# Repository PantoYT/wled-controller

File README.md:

# wled-controller

Carrier boards for an ESP32 DevKit (30-pin) running WLED with 5 V addressable strips
(WS2812B), plus printed mounts for them. The boards are generated by Python scripts against
KiCad's API, routed by a small A* router written for them, and the printed mounts are
checked for collisions against the boards' STEP models, including while the board slides in.

| | State | Where |
|---|---|---|
| rev 1.0, 1 channel | built, on the desk | [rev1/](rev1/README.md) |
| rev 2.0 `wall`, 6 channels | **current design, ready to order** | [rev2/](rev2/README.md) |
| wall mount for `wall` | designed, not printed | [enclosure/wall/](enclosure/wall/README.md) |
| base and slide-in case for rev 1.0 | printed | [enclosure/rev1/](enclosure/rev1/README.md) |

## Schematic (rev 2.0 `wall`)

[SVG](docs/schematic-wall.svg). The board is generated from code without a KiCad schematic, so
`rev2/schematic.py` draws this from a net list and `schematic.py --check` compares that list
with the routed board pad by pad (28 nets, 0 differences on 2026-10-20).

## Folders

| Folder | What is in it |
|---|---|
| `jlc/` | the one file to upload to JLCPCB |
| `rev1/` | rev 1.0: generator, router, KiCad board, STEP, Gerbers, renders, BOM |
| `rev2/` | rev 2.0: generator (`--size wall`, the old layouts still build), router, the `wall` board, its STEP, renders, back-side art in `art/` |
| `rev2/old-variants/` | layouts that were drawn and dropped: `phi` (6 ch with JST-XH), `phi4` (4 ch, status LEDs), `120`, `100` |
| `enclosure/` | printed parts, one folder per board |
| `purchases/` | costs, TME quick-buy lists (`quickbuy-v2-wall.txt` is the current one), the cost sheet |
| `footprints/`, `3d/` | footprints and stand-in 3D models shared by both revisions |
| `backups/` | WLED config and presets from the desk controller (local only, not in the repository) |

## Ordering the `wall` board at JLCPCB

Upload `jlc/wled-controller-v2-wall-gerbers.zip`: both copper, mask and silkscreen layers, the
outline and one Excellon drill file. (Locally there is also an `-art` zip with back-side art,
see [rev2/](rev2/README.md); that one is not in the repository.) JLC reads the size from the outline:
100 × 61.8 mm, inside their cheapest 100 × 100 mm bracket.

| Option | Choice |
|---|---|
| Layers | 2 |
| Thickness | 1.6 mm |
| Solder mask | black |
| Silkscreen | white |
| Surface finish | HASL lead-free is enough (no bare-copper art on this version) |
| Copper | 1 oz |
| Mark on the board | JLC prints an order number somewhere unless told otherwise; choose the option that removes it or fixes its place (check the form for its price) |

The board passed KiCad's DRC with 0 violations and 0 unconnected items (2026-10-20), with
0.2 mm clearance and 0.4 mm tracks, both inside JLC's standard limits. Optional back
art is made of 0.25 mm dots; JLC's minimum silkscreen line is 0.15 mm.

TME parts: `purchases/quickbuy-v2-wall.txt`. The rest was already on hand: 100 Ω resistors,
100 nF, two 1000 µF capacitors, the DC jack, a 2-pole 5.08 mm terminal, a 3 A blade fuse.

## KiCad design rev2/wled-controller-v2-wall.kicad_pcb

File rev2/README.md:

# wled-controller rev 2.0

Rev 2.0 drives several strips from one ESP32 DevKit (30-pin) through a 74(A)HCT245. Every
output has its own screw terminal, polyfuse and series resistor; one channel shorting trips
its polyfuse and the others keep running.

**The board to order is `wall`** (`--size wall`, files `wled-controller-v2-wall.*`, Gerbers in
`../jlc/`). The other layouts were drawn first and dropped; their boards, renders and Gerbers
are in `old-variants/`. `gen_board.py --size <x>` still builds any of them, into this folder.

## `wall` (2026-10-20, the one to order)

100 × 61.8 mm, six channels along the bottom edge, numbered right to left.

| CH | 1 | 2 | 3 | 4 | 5 | 6 |
|---|---|---|---|---|---|---|
| GPIO | 4 | 18 | 19 | 21 | 22 | 23 |

- **Per channel:** XY302R 3-pole screw terminal at the bottom edge (pins `+ D -`), RG300-16
  polyfuse (3 A hold, 5.1 A trip), 100 Ω standing resistor, the channel number, its GPIO, and
  an empty box to write the strip's name in. No JST sockets: the strips' JST SM pairs come
  with leads, and the lead goes straight into the terminal, so no cable is soldered or
  crimped; the strip unplugs at its SM connector.
- **Parts from TME or LCSC.** The footprints take either source, so the parts can come with
  the PCBs from JLC/LCSC in one parcel:

  | Part | TME | LCSC | What the footprint does |
  |---|---|---|---|
  | screw terminal 3P 3.5 mm | XY302R-3P-3.5-GN | KF350-3.5-3P (C474893) | same pads; courtyard covers both bodies (XY302R 0.7 mm behind its pins and 8.5 mm in front, KF350 3.4 / 3.5 mm); XY302R ends flush with the edge, KF350 about 6 mm inside it |
  | polyfuse 3 A | RG300-16 | FRG300-16F (C2687068) | identical size, 5.1 mm pitch |
  | mini blade fuse holder | Keystone 3568 | XF-508P-B-B (C19727305) | Keystone's footprint with the drills opened to 1.9 mm: XFCN's 1.6 x 0.4 mm tabs sit on a 9.80 mm pitch instead of 9.92 |
  | DevKit sockets 1x15, 8.5 mm | SSW-115-01-T-S | KH-2.54FH-1X15P-H8.5 (C2932676) | standard 2.54 mm |
  | shifter, DIP-20 socket | SN74AHCT245N, 1-2199298-6 | C1548096, C72127 | standard DIP-20 |

  Lists: `../purchases/quickbuy-v2-wall.txt` (TME) and `../purchases/lcsc-bom-wall.csv` (LCSC).
- **Inputs:** the DC jack (5.5/2.1, turned so the plug goes in from the top edge, the open
  end of the wall mount) and the 2-pole screw terminal J2 next to it, in parallel before the
  main blade fuse F1. One source at a time. J2 is for a bigger supply later; the jack has no
  current rating at TME.
- **Main fuse:** 7.5 A at most (track rating, see Power); with the current 3 A supply use the
  spare 3 A fuse.
- **Shifter:** SN74HCT245N or SN74AHCT245N in a socket (HC does not work: it does not see
  3.3 V as high at 5 V). The two unused buffers have their inputs on GND.
- **Nothing tall under the DevKit.** The DevKit sits on one 8.5 mm female header plus its own
  2.5 mm pin plastic, so its underside is 11 mm above the board. C1 (EEUFR1C102L, 11.5 mm
  tall) sits left of the shifter; only the DevKit's own sockets are inside its outline.
- **Mounting holes** H1-H4 at (3.5, 21.0), (3.5, 33.0), (96.52, 39.37), (96.52, 57.15): the
  wall mount's posts, placed where nothing below them passes over a post while the board
  slides in.
- **Back:** "panto", panto-dev.com and the channel to GPIO table. Optional back art:
  `python art/make_art.py picture.png` dithers any picture onto a 0.25 mm grid
  (`art/silk-runs.json`); `gen_board.py --size wall --art art/silk-runs.json` then builds
  `wled-controller-v2-wall-art`, with the art mirrored onto the back silkscreen and cut away
  round every pad and hole pixel by pixel, and `route.py --size wall --art` routes it. The
  board Panto orders carries a wallpaper that is not his to publish, so the picture, the
  `-art` board and its Gerbers stay out of this repository. Silkscreen art costs nothing extra
  at JLC: it is the same white layer.
- **Schematic:** `python schematic.py` draws `../docs/schematic-wall.svg/.png` from the net list
  in the script (schemdraw); `schematic.py --check`, run with KiCad's Python, compares that
  list with the routed board and exits 1 on any difference.
- **Outputs:** `python fab.py wled-controller-v2-wall` writes `../jlc/<name>-gerbers.zip`
  (fails if no drill file came out), the STEP and the renders.
- Routed by `route.py --size wall`: DRC 0 violations, 0 unconnected (2026-10-20). The strip
  terminals' GND pins join the pours solid (they carry the strip current, and the tracks
  starved their thermal spokes).

## `phi4` (dropped 2026-10-20, in `old-variants/`)

Kept for the record; Panto rejected the status LEDs, the gold logo and pixel row, the
hard-coded channel names and the four channels. Its XY302R footprint, wall-mount edge margins
and solid terminal GND carried over to `wall`.

Same 100 × 61.8 mm outline as `phi` (JLC's cheapest bracket), cut down to what the desk and
the TV need, with room for status LEDs and a wall mount (`../enclosure/wall/`):

| CH | GPIO | Strip | LEDs |
|---|---|---|---|
| 1 DESK | 4 | desk, segments as on rev 1.0 | 72 |
| 2 ASUS | 18 | monitor top and sides, from the 1.6 m left over | ~40 |
| 3 TV | 19 | TV perimeter 2 × 91 + 2 × 53 cm, new strip | ~86 |
| 4 AUX | 21 | spare | |

What changed against `phi`:

- **4 channels, not 6.** Three are used; the fourth is a spare. Each cell is 16.5 mm wide
  instead of 12.
- **No JST-XH sockets.** The strips plug in through JST SM pairs, and the pair's pigtail goes
  into the screw terminal, so a strip still unplugs at its SM connector with no hand-made
  leads. JST SM has no PCB socket (wire-to-wire series).
- **No DC jack.** Power comes in through J2 only (Mean Well GST60A05-P1J, 5 V 6 A, through a
  DC-plug-to-screw-terminal adapter). The PC-GK2.1 jack has no current rating at TME, and the
  left edge has to be free for the mount's rail.
- **XY302R terminals with their own footprint**
  (`../footprints/wled.pretty/TerminalBlock_Xinya_XY302R-3_P3.50mm_Horizontal`). From the
  Xinlaiya drawing: pins 0.9 × 0.5 mm (1.03 mm diagonal, fits the 1.2 mm drill), 0.7 mm from
  the back face, body 9.2 mm deep. The pads match KiCad's Phoenix PT footprint, but the body
  does not: on the Phoenix footprint an XY302R would overhang the board edge by about 3 mm.
  The wire entries now end 1.2 mm inside the bottom edge.
- **4 A polyfuses** (`RG400-16`: 4 A hold, 6.8 A trip, same 5.1 mm pitch) and 2.0 mm V_CHn
  tracks, so the TV strip is not capped at 3 A.
- **Two status LEDs per channel**, 3 mm through-hole: yellow DATA on the left, green PWR on
  the right. PWR (10 kΩ from V_CHn) shows that the channel's polyfuse passes current: dark
  means tripped or no input. DATA (470 Ω) hangs on one of the 74HCT245's four spare buffers,
  whose inputs copy that channel's GPIO, so the LED never loads the strip's data line. It
  glows while WLED sends frames (dimly: a frame is a few ms) and stays dark when nothing is
  sent. Values chosen from what is on hand (parts-inventory: 470 Ω × 10, 10 kΩ × 20,
  5 green, 5 yellow); a brighter PWR LED is 1 kΩ.
- **Look:** black mask, ENIG, the logo and a row of 15 "pixels" sized like the desk's fill-in
  wave are bare copper with the mask opened, so they come out gold. Channel names on the
  front, the channel → GPIO → name table on the back.
- **C2 moved 5 mm right** so the mount's post under H4 does not run into its lead while the
  board slides in.

Routed by `route.py --size phi4`, DRC 0 violations, 0 unconnected (2026-10-20). The strip
terminals' GND pins and the LED cathodes join the pours solid, not through thermal spokes:
the router's tracks starved their spokes, and the terminal GND carries the strip current.
Gerbers: `old-variants/wled-controller-v2-phi4-gerbers.zip`. TME list: `../purchases/old/quickbuy-v2-phi4.txt`.

WLED settings for this board: LED Preferences, four outputs (GPIO 4, 18, 19, 21), "Use
per-output limiter" on, a limit per output under the 4 A polyfuses: TV 3500 mA, desk
2500 mA, ASUS 1000 mA. With the per-output limiter WLED has no separate total (its settings
page shows the sum, 7000 mA here), so the 6 A supply is kept by the interlock planned in rice:
the desk group (CH1 + CH2, 3500 mA) and the TV (3500 mA) never light at once.

## Power

`VIN_RAW` and `+5V` are 2.6 mm tracks on 1 oz outer copper: about 6.5 A at a 20 °C rise and
7.8 A at 30 °C (IPC-2221). The main fuse is therefore 7.5 A at most, printed next to F1 on the
`phi` board. 3 mm tracks no longer routed on `phi` (15 unconnected), 2.6 mm does with DRC
clean (2026-10-16). TME gives no current rating for the PC-GK2.1 jack; small barrel jacks are
usually a few amps, so heavy loads should come in through the screw terminal J2. The `120` and
`100` boards were not regenerated with the wider tracks.

Renders: `kicad-cli pcb render --use-board-stackup-colors --floor --background opaque ...`
(without `--use-board-stackup-colors` the black mask comes out olive).

## What changed from rev 1.0

From the rev 1.0 build notes:

- **Main fuse outside the module.** F1 sits in the input row and nothing tall is under the
  DevKit, so the module sits in one female header row, one contact.
- **Thermal reliefs everywhere**, the ESP32's GND and power pins included. The router also
  keeps a wider ring free around GND pads, so their spokes into the pours survive.
- **Black solder mask** in the stackup.
- **No hand-made pigtails.** Each channel has a PCB-mounted JST-XH 3-pin socket next to its
  screw terminal.
- **Independent outputs.** Each channel has its own GPIO, buffer, resistor and polyfuse,
  where rev 1.0 had one GPIO driving four copies.

Inputs are the DC jack and a 5.08 mm screw terminal, in parallel before F1. The solder pads
and the pin header input are gone.

## Parts for the old `phi` board (6 channels with JST-XH), TME, 2026-10-16

Prices are gross PLN from the TME API, at the quantity in the table,
which is TME's minimum where that is more than the board needs. Nothing was ordered.

| Ref | Part | TME symbol | Qty | PLN |
|---|---|---|---|---|
| U1 | 74HCT245, DIP-20. **HCT or AHCT**: plain HC does not see 3.3 V as high at 5 V | `SN74HCT245N` | 1 | 2.70 |
| — | DIP-20 socket | `1-2199298-6` | 1 | 2.29 |
| F1 | Mini blade fuse holder | `KEYS3568` | 1 | 4.80 |
| — | Mini blade fuse 7.5 A, at most (see Power) | `029707.5WXNV` | 2 | ~3.4 |
| F11-F16 | Polyfuse 3 A hold, 5.1 A trip, 16 V, 5.1 mm pitch (fits the MF-RG300 footprint) | `RG300-16` | 6 | 8.19 |
| J11-J16 | Screw terminal 3.5 mm, 3-pole, horizontal | `XY302R-3P-3.5-GN` | 6 | 7.76 |
| J21-J26 | JST XH 3-pin socket, vertical | `B3B-XH-A` | 6 | 2.97 |
| R1-R6 | 100 Ω 0.25 W, mounted standing | `CF1/4W-100R` | 100 | 4.03 |
| C1, C2 | 1000 µF 16 V, Ø8 mm, 5 mm pitch (C2 on 3V3) | `EEUFR1C102L` | 2 | 7.90 |
| C3 | 100 nF ceramic, 5 mm pitch | `CC-104/100` | 100 | 17.11 |
| J1 | DC jack 5.5/2.1 (footprint in `../footprints`) | `PC-GK2.1` | 3 | 5.26 |
| J2 | Screw terminal 5.08 mm, 2-pole | `TB-5.08-P-2P/BL` | 5 | 6.61 |
| U2, U3 | Female header 1×40, cut into two 1×15 | `ZL262-40SG` | 2 | 4.47 |
| | **Total** | | | **77.51** |

Without what is left over from rev 1.0 (resistors, 100 nF, DC jacks, 2-pole terminals,
headers, 1000 µF capacitors, a spare fuse holder) the new parts come to about 27 PLN:
74HCT245, socket, fuses, polyfuses, 3.5 mm terminals and XH sockets. Shipping and the PCB
are on top. The 120 and 100 boards need 8 of each per-channel part.

Notes:

- The footprint is Phoenix PT 1,5/3-3,5-H, which TME lists (`PT1.5/3-3.5-H`, 3.92 PLN) but
  had 0 in stock; XY302R is the in-stock 3.5 mm alternative. Its hole and pad sizes are not
  checked against the Phoenix footprint yet. "1,5" in the Phoenix name is the 1.5 mm² wire
  rating; strip leads (AWG 22-18, 0.3-0.8 mm²) fit.
- The strips' own connectors are **JST SM**, a wire-to-wire series (JST's SM datasheet:
  "wire-to-wire connectors"); there is no SM socket for a PCB. The board has JST **XH**
  sockets, which take an XH plug, so each strip needs an SM-to-XH adapter lead.
- MF-RG300 (the footprint's part) is not at TME; RG300-16 has the same 5.1 mm pitch and
  1.2 mm lead offset.

Pin order on every terminal and socket is `+ D -` (pad 1 is +).

## Generating

KiCad 10's bundled Python, one size at a time:

```
"C:/Program Files/KiCad/10.0/bin/python.exe" gen_board.py --size phi
"C:/Program Files/KiCad/10.0/bin/python.exe" route.py --size phi
kicad-cli pcb drc --refill-zones --save-board wled-controller-v2-phi.kicad_pcb
```

`gen_board.py` overwrites the board. `route.py` is rev 1.0's grid A* router without its
hand-drawn presets. It lays a few GND stubs first (C3, U1's GND pin, the ESP32's GND pins),
routes every net, adds GND stitching vias, then fills the pours and routes a GND track to
any GND pad that tracks closed off from the main pour on both layers. All three boards:
every net routed, DRC 0 violations, 0 unconnected (2026-10-16).

## Log, 2026-10-16

- Started from rev 1.0's generator and router; added the channel strip, the three layouts
  (`--size`), the ESP32 on its side for `phi`, and unused '245 inputs tied to GND.
- Fixed on the way: floating GND copper (island removal on, 0.5 mm minimum pour width),
  C3's GND pad and the ESP32's GND pins fenced in (GND stubs before routing), U1's GND pin
  closed in on the 120 board (U1 turned 90 there, so its input row faces the ESP32).
- Mask colour `#0A0A0CF0` instead of "Black": KiCad renders its "Black" brown. JLC's black
  mask is black either way.
- C1 is Ø8 like C2, so rev 1.0's 1000 µF 16 V capacitors fit both.
- Open: check XY302R against the footprint, pick the board (Panto leans to `phi`), a base
  for it (rev 2.0's holes are not where rev 1.0's are), and maybe per-channel LEDs.

The 3D view uses the stand-in DevKit models from `../3d`. The polyfuses have no 3D model.

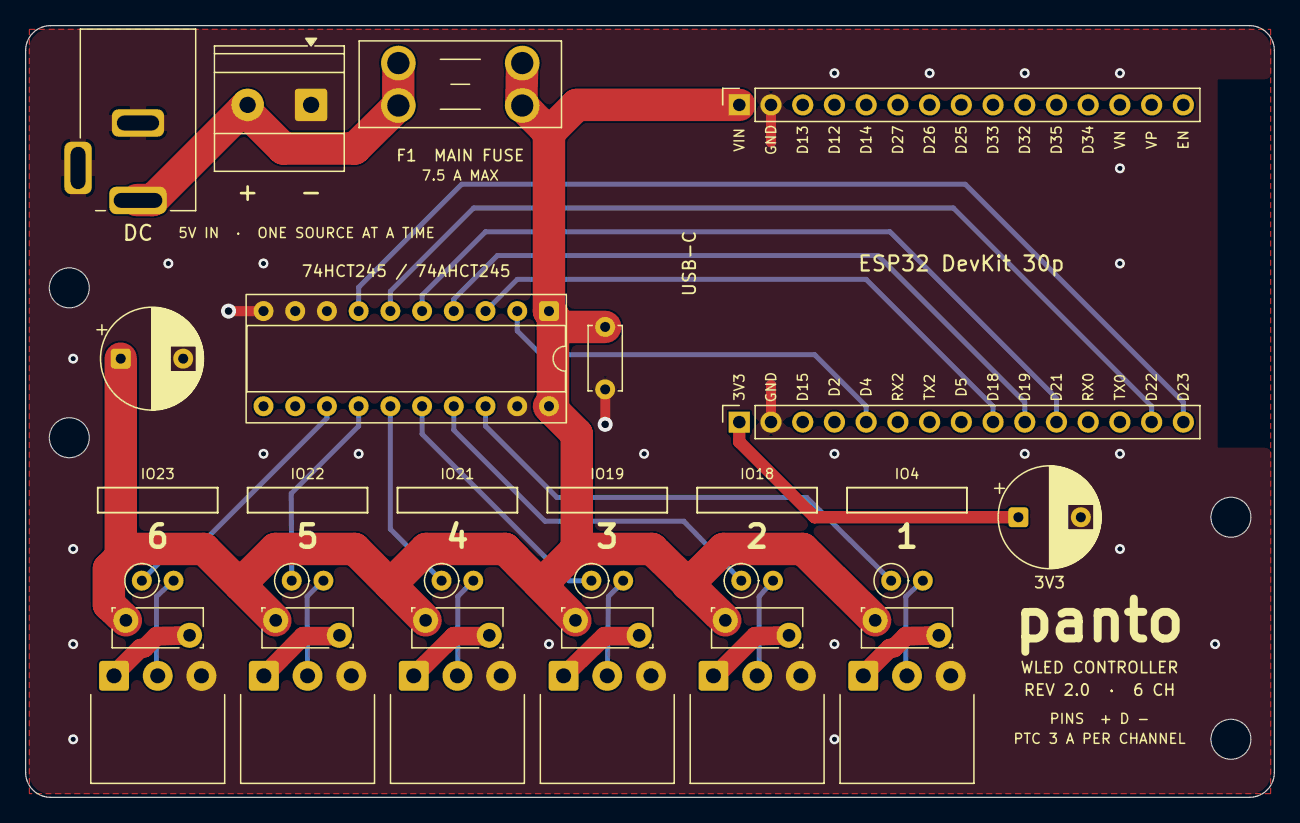
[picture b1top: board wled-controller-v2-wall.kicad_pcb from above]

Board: 2 copper layers, 100.0 x 61.8 mm, 32 parts (0 on the bottom side), 28 nets.

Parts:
C1, C2: 1000uF 16V; CP_Radial_D8.0mm_P5.00mm
C3: 100nF; C_Disc_D5.0mm_W2.5mm_P5.00mm
ESP1: ESP32 DevKit (3D only)
F1: Mini blade fuse, 7.5 A max; Fuseholder_Blade_Mini_Keystone_3568
F11, F12, F13, F14, F15, F16: RG300-16 3A; Fuse_Bourns_MF-RG300
H1, H2, H3, H4: M3; MountingHole_3.2mm_M3
J1: PC-GK2.1; DC_Jack_Ninigi_PC-GK2.1
J2: Screw 2p IN; TerminalBlock_Phoenix_MKDS-1,5-2-5.08_1x02_P5.08mm_Horizont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
J11: Screw CH1; TerminalBlock_Xinya_XY302R-3_P3.50mm_Horizontal
J12: Screw CH2; TerminalBlock_Xinya_XY302R-3_P3.50mm_Horizontal
J13: Screw CH3; TerminalBlock_Xinya_XY302R-3_P3.50mm_Horizontal
J14: Screw CH4; TerminalBlock_Xinya_XY302R-3_P3.50mm_Horizontal
J15: Screw CH5; TerminalBlock_Xinya_XY302R-3_P3.50mm_Horizontal
J16: Screw CH6; TerminalBlock_Xinya_XY302R-3_P3.50mm_Horizontal
R1, R2, R3, R4, R5, R6: 100R; R_Axial_DIN0207_L6.3mm_D2.5mm_P2.54mm_Vertical
U1: 74HCT245; DIP-20_W7.62mm_Socket
U2, U3: ESP32 socket; PinSocket_1x15_P2.54mm_Vertical

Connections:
+3V3: C2.1, U2.1
+5V: C1.1, C3.1, F1.2, F11.1, F12.1, F13.1, F14.1, F15.1, F16.1, U1.1, U1.20, U3.1
DATA1: J11.2, R1.2
DATA2: J12.2, R2.2
DATA3: J13.2, R3.2
DATA4: J14.2, R4.2
DATA5: J15.2, R5.2
DATA6: J16.2, R6.2
GND: C1.2, C2.2, C3.2, J1.2, J1.3, J2.1, J11.3, J12.3, J13.3, J14.3, J15.3, J16.3, U1.8, U1.9, U1.10, U1.19, U2.2, U3.2
IO_CH1: U1.2, U2.5
IO_CH2: U1.3, U2.9
IO_CH3: U1.4, U2.10
IO_CH4: U1.5, U2.11
IO_CH5: U1.6, U2.14
IO_CH6: U1.7, U2.15
OUT1_RAW: R1.1, U1.18
OUT2_RAW: R2.1, U1.17
OUT3_RAW: R3.1, U1.16
OUT4_RAW: R4.1, U1.15
OUT5_RAW: R5.1, U1.14
OUT6_RAW: R6.1, U1.13
VIN_RAW: F1.1, J1.1, J2.2
V_CH1: F11.2, J11.1
V_CH2: F12.2, J12.1
V_CH3: F13.2, J13.1
V_CH4: F14.2, J14.1
V_CH5: F15.2, J15.1
V_CH6: F16.2, J16.1

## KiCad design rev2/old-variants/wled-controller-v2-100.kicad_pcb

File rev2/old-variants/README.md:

# Dropped rev 2.0 layouts

Drawn with `../gen_board.py` and `../route.py` before `wall` was chosen. Not to be ordered.

| `--size` | Board | Channels | GPIO, CH1 first | Why dropped |
|---|---|---|---|---|
| `phi` | 100 × 61.8 mm | 6, screw terminal + JST-XH each | 4, 18, 19, 21, 22, 23 | XH sockets need SM-to-XH leads made by hand; jack faces the left edge, where the wall mount's rail goes |
| `phi4` | 100 × 61.8 mm | 4, status LEDs, gold logo | 4, 18, 19, 21 | too few channels, LEDs and gold art not wanted |
| `120` | 120 × 74.16 mm | 8 | 4, 32, 33, 25, 26, 27, 14, 13 | too big, past JLC's 100 × 100 mm price bracket |
| `100` | 100 × 100 mm | 8 | 4, 32, 33, 25, 26, 27, 14, 13 | a square, not liked |

`120` and `100` were not regenerated with the 2.6 mm power tracks. The boards here point their
3D models at `../../3d/`; regenerating any of them writes into `../`, not into this folder.

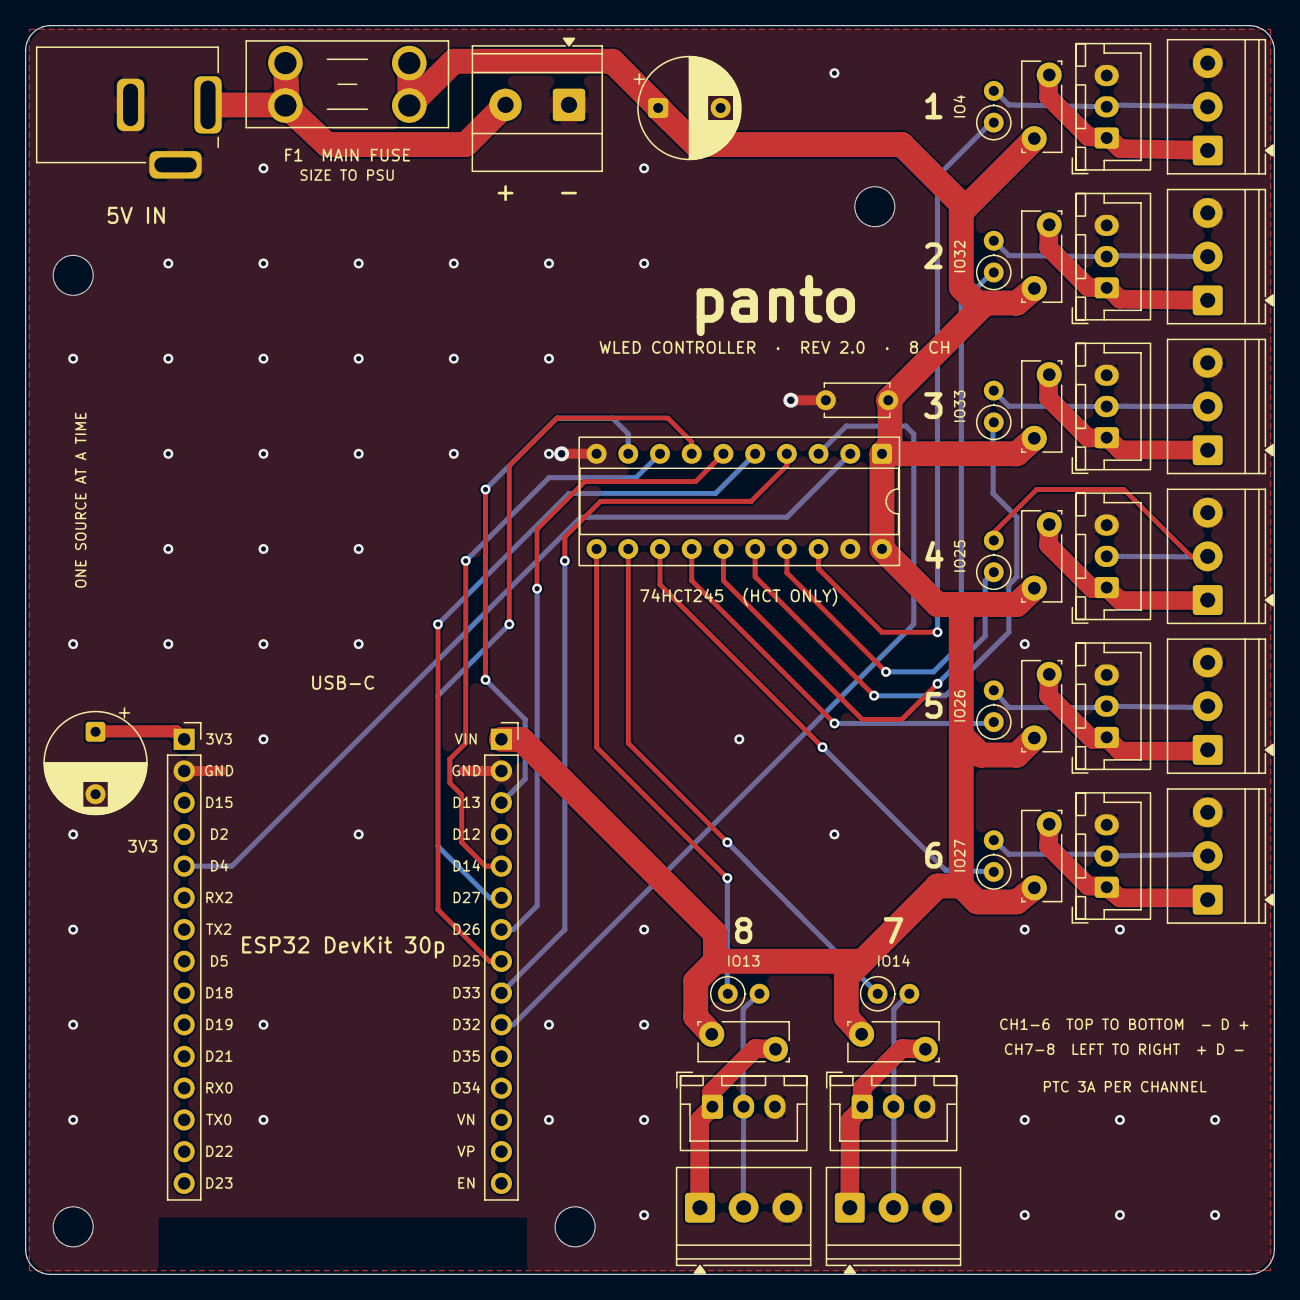
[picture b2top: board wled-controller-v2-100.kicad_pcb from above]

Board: 2 copper layers, 100.0 x 100.0 mm, 46 parts (0 on the bottom side), 36 nets.

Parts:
C1, C2: 1000uF 16V; CP_Radial_D8.0mm_P5.00mm
C3: 100nF; C_Disc_D5.0mm_W2.5mm_P5.00mm
ESP1: ESP32 DevKit (3D only)
F1: Mini blade fuse, size to the PSU; Fuseholder_Blade_Mini_Keystone_3568
F11, F12, F13, F14, F15, F16, F17, F18: MF-RG300 3A; Fuse_Bourns_MF-RG300
H1, H2, H3, H4: M3; MountingHole_3.2mm_M3
J1: PC-GK2.1; DC_Jack_Ninigi_PC-GK2.1
J2: Screw 2p IN; TerminalBlock_Phoenix_MKDS-1,5-2-5.08_1x02_P5.08mm_Horizont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
J11: Screw CH1; TerminalBlock_Phoenix_PT-1,5-3-3.5-H_1x03_P3.50mm_Horizontal
J12: Screw CH2; TerminalBlock_Phoenix_PT-1,5-3-3.5-H_1x03_P3.50mm_Horizontal
J13: Screw CH3; TerminalBlock_Phoenix_PT-1,5-3-3.5-H_1x03_P3.50mm_Horizontal
J14: Screw CH4; TerminalBlock_Phoenix_PT-1,5-3-3.5-H_1x03_P3.50mm_Horizontal
J15: Screw CH5; TerminalBlock_Phoenix_PT-1,5-3-3.5-H_1x03_P3.50mm_Horizontal
J16: Screw CH6; TerminalBlock_Phoenix_PT-1,5-3-3.5-H_1x03_P3.50mm_Horizontal
J17: Screw CH7; TerminalBlock_Phoenix_PT-1,5-3-3.5-H_1x03_P3.50mm_Horizontal
J18: Screw CH8; TerminalBlock_Phoenix_PT-1,5-3-3.5-H_1x03_P3.50mm_Horizontal
J21: JST-XH CH1; JST_XH_B3B-XH-A_1x03_P2.50mm_Vertical
J22: JST-XH CH2; JST_XH_B3B-XH-A_1x03_P2.50mm_Vertical
J23: JST-XH CH3; JST_XH_B3B-XH-A_1x03_P2.50mm_Vertical
J24: JST-XH CH4; JST_XH_B3B-XH-A_1x03_P2.50mm_Vertical
J25: JST-XH CH5; JST_XH_B3B-XH-A_1x03_P2.50mm_Vertical
J26: JST-XH CH6; JST_XH_B3B-XH-A_1x03_P2.50mm_Vertical
J27: JST-XH CH7; JST_XH_B3B-XH-A_1x03_P2.50mm_Vertical
J28: JST-XH CH8; JST_XH_B3B-XH-A_1x03_P2.50mm_Vertical
R1, R2, R3, R4, R5, R6, R7, R8: 100R; R_Axial_DIN0207_L6.3mm_D2.5mm_P2.54mm_Vertical
U1: 74HCT245; DIP-20_W7.62mm_Socket
U2, U3: ESP32 socket; PinSocket_1x15_P2.54mm_Vertical

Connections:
+3V3: C2.1, U2.1
+5V: C1.1, C3.1, F1.2, F11.1, F12.1, F13.1, F14.1, F15.1, F16.1, F17.1, F18.1, U1.1, U1.20, U3.1
DATA1: J11.2, J21.2, R1.2
DATA2: J12.2, J22.2, R2.2
DATA3: J13.2, J23.2, R3.2
DATA4: J14.2, J24.2, R4.2
DATA5: J15.2, J25.2, R5.2
DATA6: J16.2, J26.2, R6.2
DATA7: J17.2, J27.2, R7.2
DATA8: J18.2, J28.2, R8.2
GND: C1.2, C2.2, C3.2, J1.2, J1.3, J2.1, J11.3, J12.3, J13.3, J14.3, J15.3, J16.3, J17.3, J18.3, J21.3, J22.3, J23.3, J24.3, J25.3, J26.3, J27.3, J28.3, U1.10, U1.19, U2.2, U3.2
IO_CH1: U1.2, U2.5
IO_CH2: U1.3, U3.10
IO_CH3: U1.4, U3.9
IO_CH4: U1.5, U3.8
IO_CH5: U1.6, U3.7
IO_CH6: U1.7, U3.6
IO_CH7: U1.8, U3.5
IO_CH8: U1.9, U3.3
OUT1_RAW: R1.1, U1.18
OUT2_RAW: R2.1, U1.17
OUT3_RAW: R3.1, U1.16
OUT4_RAW: R4.1, U1.15
OUT5_RAW: R5.1, U1.14
OUT6_RAW: R6.1, U1.13
OUT7_RAW: R7.1, U1.12
OUT8_RAW: R8.1, U1.11
VIN_RAW: F1.1, J1.1, J2.2
V_CH1: F11.2, J11.1, J21.1
V_CH2: F12.2, J12.1, J22.1
V_CH3: F13.2, J13.1, J23.1
V_CH4: F14.2, J14.1, J24.1
V_CH5: F15.2, J15.1, J25.1
V_CH6: F16.2, J16.1, J26.1
V_CH7: F17.2, J17.1, J27.1
V_CH8: F18.2, J18.1, J28.1

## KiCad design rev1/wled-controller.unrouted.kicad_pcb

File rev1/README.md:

# wled-controller rev 1.0 (built, on the desk)

A 100 × 61.8 mm (golden rectangle) two-layer carrier board for an ESP32 DevKit (30-pin) running WLED
with 5 V addressable LED strips (WS2812B and similar). It follows the classic
WLED wiring diagram by @DedeHai: fused 5 V input, bulk capacitors on 5 V and
3.3 V, a 74AHCT125 level shifter and series data resistors.

Prices and where to buy: [BOM.md](BOM.md). Rev 2.0: [../rev2/](../rev2/README.md). Enclosure and desk base: [../enclosure/rev1/](../enclosure/rev1/README.md).

## What is on the board

- **Power input** (all in parallel, before the fuse; use one at a time):
  DC jack 5.5/2.1 mm, 2-pin screw terminal, solder pads, 2-pin header (max 3 A).
- **F1**: mini blade fuse, sized to the power supply (3 A for a 5 V / 3 A PSU).
- **ESP32 DevKit** in two 1×15 female headers, 25.4 mm row spacing, USB-C facing the top edge,
  3V3 capacitor on the left, VIN capacitor on the right.
- **U1 74AHCT125**: GPIO4 (D4) drives all four buffers, and each has its own series resistor:
  - MAIN: solder pads with strain relief for a JST SM pigtail (+, D, −)
  - SCREW: separate blocks on the right edge: 3× +, 3× −, and a D + − pair
  - SOLDER: D, 3× −, 3× +
  - PINS: 7-pin header `+ + + D − − −`
- Back silkscreen: "panto" (optional pixel-art outline with `--gear path.png`).
- GND pours on both layers and a copper keepout under the ESP32 antenna.

## Bill of materials

| Ref | Part | Qty |
|---|---|---|
| U1 | SN74AHCT125N (DIP-14). **Must be AHCT or HCT**, plain HC will not work | 1 |
| — | DIP-14 socket | 1 |
| U2, U3 | Female header 1×15, 2.54 mm | 2 |
| C1, C2 | 1000 µF 16 V electrolytic, Ø8 mm, 5 mm pitch | 2 |
| C3 | 100 nF ceramic (MLCC), 5 mm pitch | 1 |
| R1–R4 | 100 Ω 0.25 W axial (33–200 Ω works) | 4 |
| F1 | Mini blade fuse holder, Keystone 3568 footprint, plus 3 A mini blade fuse | 1 |
| J1 | DC barrel jack 5.5/2.1 mm, PCB mount (DC-005 style) | 1 |
| J2, J6–J8 | Screw terminals 5.08 mm: 2× 3-pole, 2× 2-pole | 4 |
| J4, J12 | Male pin header 1×2 and 1×7 | 1 each |
| J5 | JST SM 3-pin pigtail (female side soldered into the board) | 1 |
| H1–H4 | M3 standoffs (optional) | 4 |

## Regenerating

`gen_board.py` builds the unrouted board with KiCad's bundled Python:

```
"C:/Program Files/KiCad/10.0/bin/python.exe" gen_board.py --gear path/to/gear.png
```

It **overwrites** `wled-controller.kicad_pcb`, so do not run it after routing has started.
Set `KICAD10_FOOTPRINT_DIR` if KiCad is installed somewhere else.

## 3D model

The 3D view shows the chip in its socket, a 3 A fuse and a stand-in ESP32 DevKit
(KiCad's WROOM-32 model on simple boxes from `../3d/make_boxes.py`). The stand-in is the
`ESP1` footprint: board-only, no pads, excluded from BOM and position files.
`gen_board.py --mask Purple` changes the solder mask colour used by the 3D view.

## Routing

`route.py` is a small grid A* router (numpy, KiCad's bundled Python). It routes every
net except GND, which the pours on both layers pick up, then adds GND stitching vias:

```
cp wled-controller.unrouted.kicad_pcb wled-controller.kicad_pcb
"C:/Program Files/KiCad/10.0/bin/python.exe" route.py
kicad-cli pcb drc --refill-zones --save-board wled-controller.kicad_pcb
```

Power nets are 1.5 mm (VIN_RAW, +5V) and 1.0 mm (+3V3), signals 0.4 mm.
`wled-controller-gerbers.zip` holds the Gerbers and drill file for the fab.

## Before ordering

- Measure your ESP32's row spacing and compare the pin labels on the silkscreen with
  your board. `ESP_ROW_SPACING` in the script sets the spacing.
- Import `wled-controller.step` into your CAD tool to design an enclosure around it.
- Check the polarity of the DC plug with a multimeter. The board expects centre positive.
- In WLED, set the LED output to GPIO4 and cap the current limit at about 2500 mA for a 3 A supply.

## Rev 1.0 build notes (2026-10-14)

Board #1 was hand-soldered and drives a strip without flicker. Problems found on the way,
as input for v2:

- **Fuse holder under the ESP32.** The KEYS3568 holder sits under the overhanging end of
  the DevKit, so the ESP32 needs a second layer of female headers to clear it. The extra
  contact made VIN unreliable (the board only worked while the ESP32 was pushed sideways);
  bending the extra header's VIN leg slightly fixed it. v2: every tall part outside the
  ESP32 outline, one contact between module and board.
- **Cold joints on the power pins.** The first pads of both header rows (3V3, VIN, GND)
  sit on wide power traces and pour; at normal iron temperature the solder did not wet.
  v2: thermal reliefs on those pads, or solder them at 360-370 °C.
- **White solder mask** shows flux residue and turns yellow around joints. Pick black or
  green.
- **Lead time.** A month of waiting for one board order; order at least 2-3 sets of every
  part, and more than one board revision in the same order when possible.
- **Strip cable.** The board should not hang behind the desk: add a 0.5 m JST SM 3-pin
  extension.

## v2 ideas

- at least 4 independent outputs (separate GPIOs, not copies of one signal), possibly
  room for two ESP32 boards;
- fuse moved away from the module, ideally a main fuse plus protection per output;
- connectors that do not need hand-made pigtails.

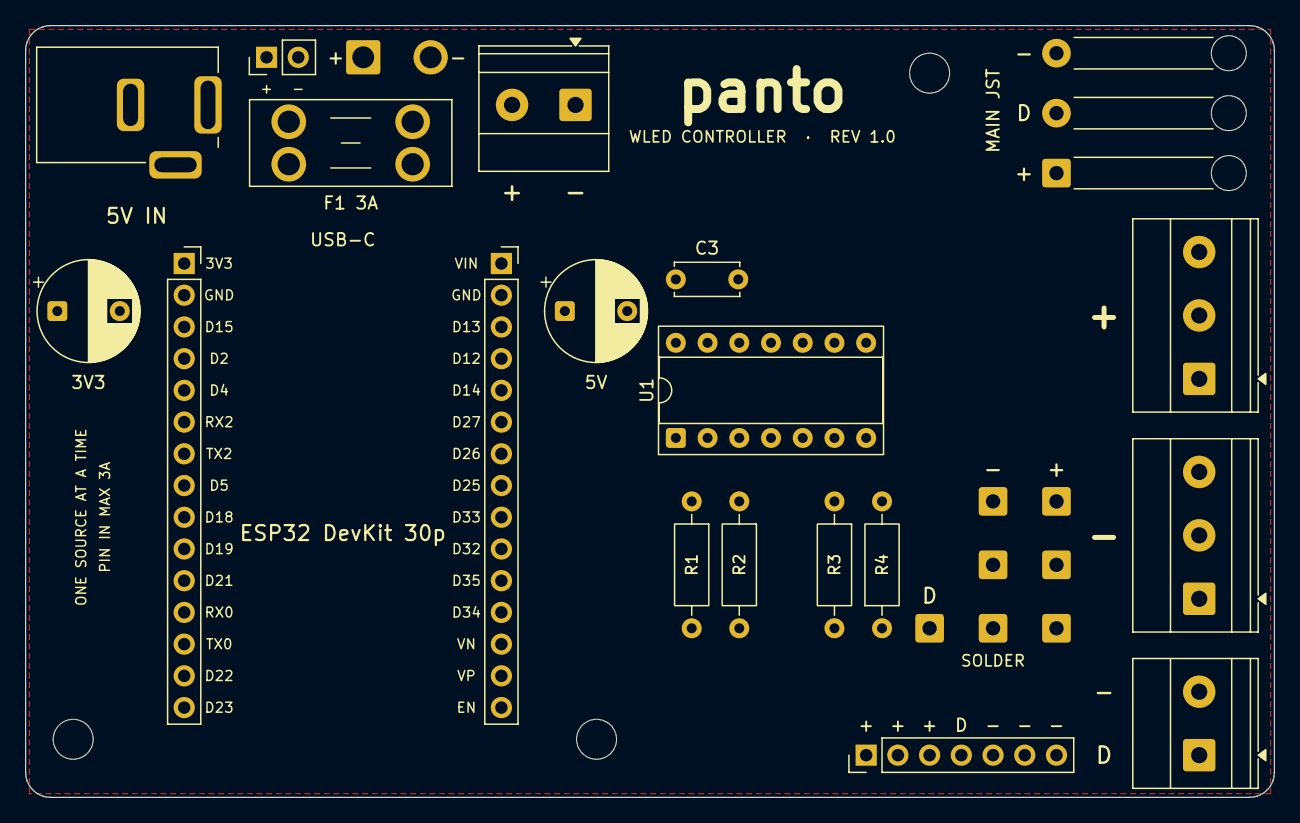
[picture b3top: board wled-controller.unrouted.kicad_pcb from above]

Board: 2 copper layers, 100.0 x 61.8 mm, 31 parts (0 on the bottom side), 13 nets, no tracks yet.

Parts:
C1, C2: 1000uF 16V; CP_Radial_D8.0mm_P5.00mm
C3: 100nF; C_Disc_D5.0mm_W2.5mm_P5.00mm
ESP1: ESP32 DevKit (3D only)
F1: Fuse 3A (mini blade); Fuseholder_Blade_Mini_Keystone_3568
H1, H2, H3: M3; MountingHole_3.2mm_M3
J1: PC-GK2.1; DC_Jack_Ninigi_PC-GK2.1
J2: Screw 2p IN; TerminalBlock_Phoenix_MKDS-1,5-2-5.08_1x02_P5.08mm_Horizont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
J3: Solder IN; SolderWire-1sqmm_1x02_P5.4mm_D1.4mm_OD2.7mm
J4: Pin IN; PinHeader_1x02_P2.54mm_Vertical
J5: JST SM pigtail MAIN; SolderWire-0.5sqmm_1x03_P4.8mm_D0.9mm_OD2.3mm_Relief
J6: Screw 3p +; TerminalBlock_Phoenix_MKDS-1,5-3-5.08_1x03_P5.08mm_Horizont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
J7: Screw 3p -; TerminalBlock_Phoenix_MKDS-1,5-3-5.08_1x03_P5.08mm_Horizont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
J8: Screw D; TerminalBlock_Phoenix_MKDS-1,5-2-5.08_1x02_P5.08mm_Horizont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
J9: Solder D; SolderWire-0.5sqmm_1x01_D0.9mm_OD2.3mm
J10, J11, J12: Solder -; SolderWire-0.5sqmm_1x01_D0.9mm_OD2.3mm
J13, J14, J15: Solder +; SolderWire-0.5sqmm_1x01_D0.9mm_OD2.3mm
J16: Pin 7p; PinHeader_1x07_P2.54mm_Vertical
R1, R2, R3, R4: 100R; R_Axial_DIN0207_L6.3mm_D2.5mm_P10.16mm_Horizontal
U1: 74AHCT125; DIP-14_W7.62mm_Socket
U2, U3: ESP32 socket; PinSocket_1x15_P2.54mm_Vertical

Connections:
+3V3: C2.1, U2.1
+5V: C1.1, C3.1, F1.2, J5.1, J6.1, J6.2, J6.3, J13.1, J14.1, J15.1, J16.1, J16.2, J16.3, U1.14, U3.1
DATA1: J5.2, R4.2
DATA1_RAW: R4.1, U1.8
DATA2: J8.1, R2.2
DATA2_RAW: R2.1, U1.3
DATA3: J16.4, R1.2
DATA3_RAW: R1.1, U1.11
DATA4: J9.1, R3.2
DATA4_RAW: R3.1, U1.6
ESP_D4: U1.2, U1.5, U1.9, U1.12, U2.5
GND: C1.2, C2.2, C3.2, J1.2, J1.3, J2.1, J3.2, J4.2, J5.3, J7.1, J7.2, J7.3, J8.2, J10.1, J11.1, J12.1, J16.5, J16.6, J16.7, U1.1, U1.4, U1.7, U1.10, U1.13, U2.2, U3.2
VIN_RAW: F1.1, J1.1, J2.2, J3.1, J4.1

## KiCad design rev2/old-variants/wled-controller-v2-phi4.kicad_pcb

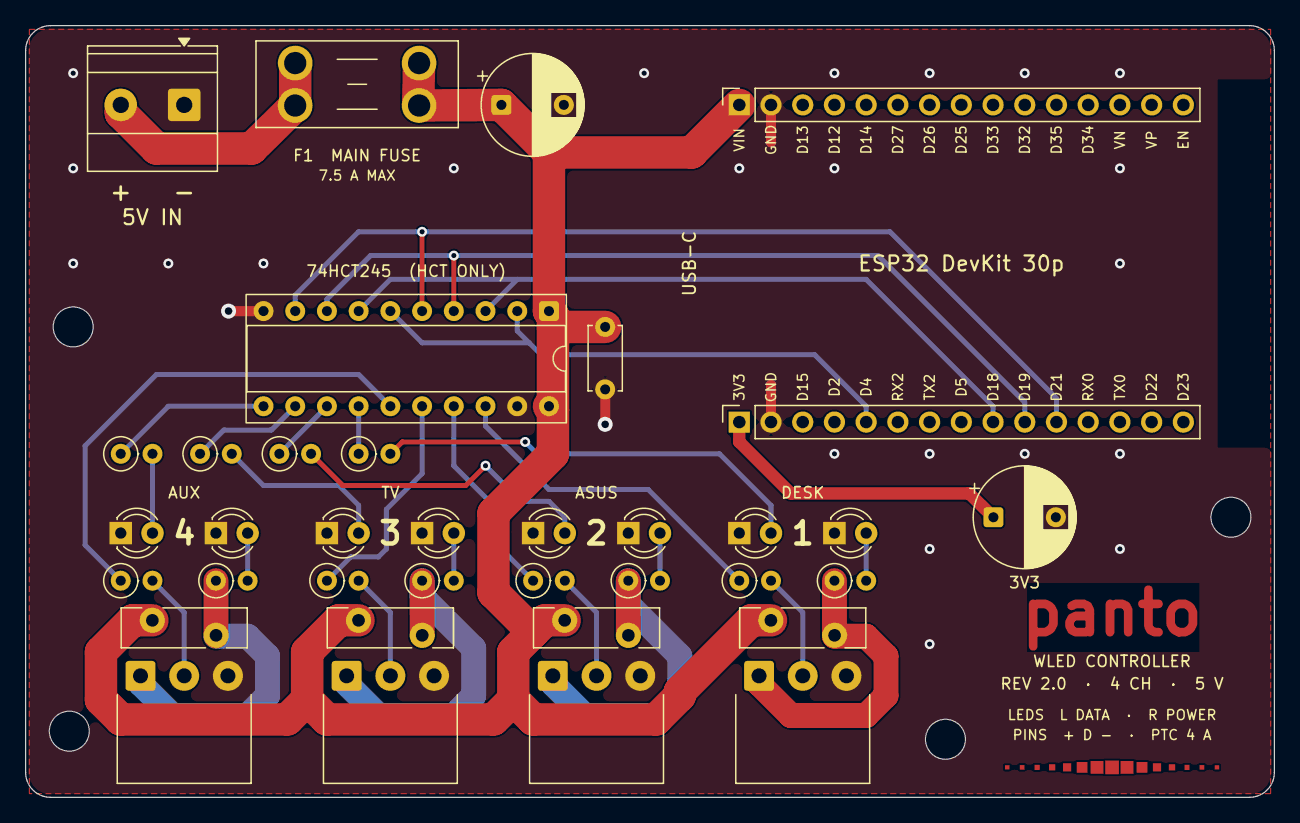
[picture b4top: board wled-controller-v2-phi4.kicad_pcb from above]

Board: 2 copper layers, 100.0 x 61.8 mm, 41 parts (0 on the bottom side), 32 nets.

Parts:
C1, C2: 1000uF 16V; CP_Radial_D8.0mm_P5.00mm
C3: 100nF; C_Disc_D5.0mm_W2.5mm_P5.00mm
D11, D12, D13, D14: LED 3mm yellow (DATA); LED_D3.0mm
D21, D22, D23, D24: LED 3mm green (PWR); LED_D3.0mm
ESP1: ESP32 DevKit (3D only)
F1: Mini blade fuse, 7.5 A max; Fuseholder_Blade_Mini_Keystone_3568
F11, F12, F13, F14: RG400-16 4A; Fuse_Bourns_MF-RG400
H1, H2, H3, H4: M3; MountingHole_3.2mm_M3
J2: Screw 2p IN; TerminalBlock_Phoenix_MKDS-1,5-2-5.08_1x02_P5.08mm_Horizont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
J11: Screw CH1; TerminalBlock_Xinya_XY302R-3_P3.50mm_Horizontal
J12: Screw CH2; TerminalBlock_Xinya_XY302R-3_P3.50mm_Horizontal
J13: Screw CH3; TerminalBlock_Xinya_XY302R-3_P3.50mm_Horizontal
J14: Screw CH4; TerminalBlock_Xinya_XY302R-3_P3.50mm_Horizontal
R1, R2, R3, R4: 100R; R_Axial_DIN0207_L6.3mm_D2.5mm_P2.54mm_Vertical
R21, R22, R23, R24: 10k; R_Axial_DIN0207_L6.3mm_D2.5mm_P2.54mm_Vertical
R31, R32, R33, R34: 470R; R_Axial_DIN0207_L6.3mm_D2.5mm_P2.54mm_Vertical
U1: 74HCT245; DIP-20_W7.62mm_Socket
U2, U3: ESP32 socket; PinSocket_1x15_P2.54mm_Vertical

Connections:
+3V3: C2.1, U2.1
+5V: C1.1, C3.1, F1.2, F11.1, F12.1, F13.1, F14.1, U1.1, U1.20, U3.1
ACT1: R31.1, U1.14
ACT2: R32.1, U1.13
ACT3: R33.1, U1.12
ACT4: R34.1, U1.11
DATA1: J11.2, R1.2
DATA2: J12.2, R2.2
DATA3: J13.2, R3.2
DATA4: J14.2, R4.2
GND: C1.2, C2.2, C3.2, D11.1, D12.1, D13.1, D14.1, D21.1, D22.1, D23.1, D24.1, J2.1, J11.3, J12.3, J13.3, J14.3, U1.10, U1.19, U2.2, U3.2
IO_CH1: U1.2, U1.6, U2.5
IO_CH2: U1.3, U1.7, U2.9
IO_CH3: U1.4, U1.8, U2.10
IO_CH4: U1.5, U1.9, U2.11
LEDA1: D11.2, R31.2
LEDA2: D12.2, R32.2
LEDA3: D13.2, R33.2
LEDA4: D14.2, R34.2
OUT1_RAW: R1.1, U1.18
OUT2_RAW: R2.1, U1.17
OUT3_RAW: R3.1, U1.16
OUT4_RAW: R4.1, U1.15
PLED1: D21.2, R21.2
PLED2: D22.2, R22.2
PLED3: D23.2, R23.2
PLED4: D24.2, R24.2
VIN_RAW: F1.1, J2.2
V_CH1: F11.2, J11.1, R21.1
V_CH2: F12.2, J12.1, R22.1
V_CH3: F13.2, J13.1, R23.1
V_CH4: F14.2, J14.1, R24.1
